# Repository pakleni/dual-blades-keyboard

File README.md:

# Dual Blades

## Images
### Keyboard Layout

### Plates

### PCB

## Features
* Split, wireless
* ZMK firmware
* nice!nano mcu
* nice!view display
* rotary encoders
* Column-staggered 44 key layout (inspired by the [Void Ergo S](https://github.com/victorlucachi/void_ergo))
* Switch-agnostic - hybrid MX/Alps PCB footprints + combo plate cutout
* Floating PCB plate
* LiPo batteries

## Firmware
[ZMK Keyboard Dual Blades](https://github.com/pakleni/zmk-keyboard-dual-blades)

## Bill of Materials

| Qty | Part |
|----:|------|
| 1 | [Matias Click Switch (box of 200)](https://matias.store/products/matias-click-switch-box-of-200) |
| 1 | [Keycap set - black blank Planck](https://matias.store/products/keycap-set-black-blank-planck) |
| 2 | [Encoder knobs](https://splitkb.com/products/knurled-metal-encoder-knob) |
| 2 | [nice!view](https://splitkb.com/products/nice-view) |
| 2 | [nice!nano](https://splitkb.com/products/nice-nano) |
| 1 | [Wireless Controller Expansion Bundle](https://splitkb.com/products/wireless-controller-expansion-bundle) |
| 1 | [THT 1N4148 diodes (100 pcs)](https://splitkb.com/products/tht-diodes) |
| 1 | [Linear rotary encoder](https://splitkb.com/products/linear-rotary-encoder) |
| 1 | [Tactile rotary encoder](https://splitkb.com/products/industrial-rotary-encoder) |
| 1 | [Reset buttons - **side push** (set of two)](https://splitkb.com/products/reset-buttons) |
| 2 | [Mill-Max Low Profile Sockets (with Headers)](https://splitkb.com/products/mill-max-low-profile-sockets) |
| 1 | [M2 screws - **4 mm**(set of 50)](https://splitkb.com/products/m2-screws) |
| 1 | [Brass M2 spacers - **8 mm** (set of 50)](https://splitkb.com/products/brass-m2-spacers) |
| 2 | [301230 LiPo (check polarity)](https://www.aliexpress.com/item/1005005348368664.html) |

## Used
* http://www.keyboard-layout-editor.com
* http://builder.swillkb.com
* https://librecad.org
* https://www.kicad.org

This work is licensed under a [Creative Commons Attribution-NonCommercial-ShareAlike 4.0 International License](https://creativecommons.org/licenses/by-nc-sa/4.0/).

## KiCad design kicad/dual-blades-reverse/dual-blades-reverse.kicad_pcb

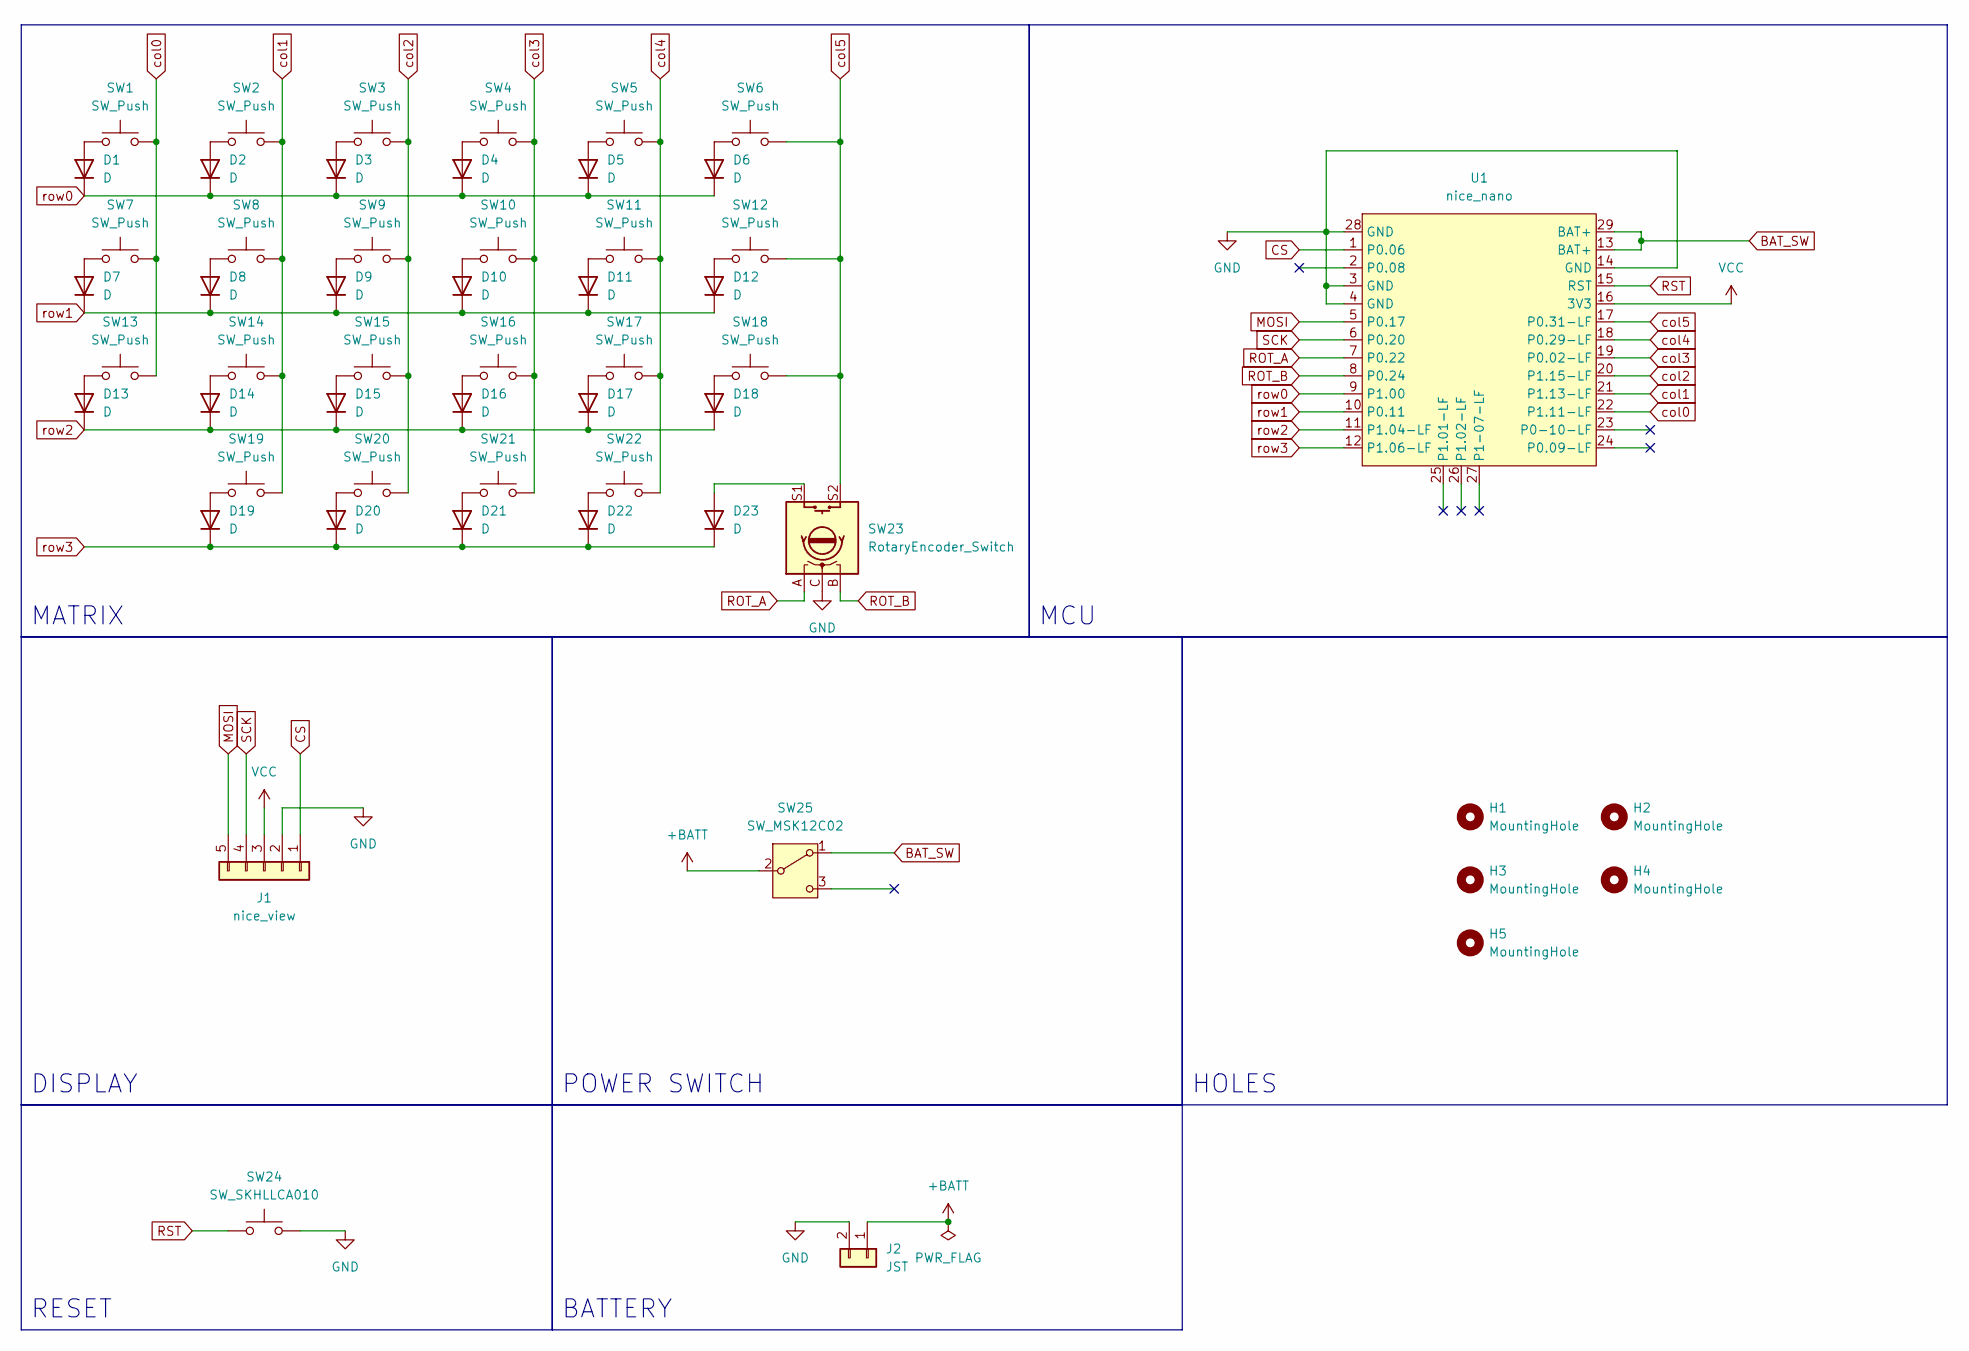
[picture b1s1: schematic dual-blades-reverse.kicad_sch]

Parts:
D1, D2, D3, D4, D5, D6, D7, D8, D9, D10, D11, D12, D13, D14, D15, D16, D17, D18, D19, D20, D21, D22, D23: D; D_DO-35_SOD27_P7.62mm_Horizontal
H1, H2, H3, H4, H5: MountingHole; MountingHole_4.3mm_M4
J1: nice_view; PinHeader_1x05_P2.54mm_Vertical
J2: JST; JST_PH_S2B-PH-K_1x02_P2.00mm_Horizontal
SW1, SW2, SW3, SW4, SW5, SW6, SW7, SW8, SW9, SW10, SW11, SW12, SW13, SW14, SW15, SW16, SW17, SW18, SW19, SW20, SW21, SW22: SW_Push; SW_Alps_MX_1u
SW23: RotaryEncoder_Switch; ROT_Alps_EC11E-Switch
SW24: SW_SKHLLCA010
SW25: SW_MSK12C02; SW_MSK12C02-HB
U1: nice_nano; nice_nano_AH_USBup

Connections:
+BATT: J2.1, SW25.2 (B)
BAT_SW: SW25.1 (A), U1.13 (BAT+), U1.29 (BAT+)
CS: J1.1, U1.1 (P0.06)
GND: J1.2, J2.2, SW23.C, SW24.2, U1.3 (GND), U1.4 (GND), U1.14 (GND), U1.28 (GND)
MOSI: J1.5, U1.5 (P0.17)
unnamed: D1.2 (A), SW1.1
unnamed: D2.2 (A), SW2.1
unnamed: D3.2 (A), SW3.1
unnamed: D4.2 (A), SW4.1
unnamed: D5.2 (A), SW5.1
unnamed: D6.2 (A), SW6.1
unnamed: D7.2 (A), SW7.1
unnamed: D8.2 (A), SW8.1
unnamed: D9.2 (A), SW9.1
unnamed: D10.2 (A), SW10.1
unnamed: D11.2 (A), SW11.1
unnamed: D12.2 (A), SW12.1
unnamed: D13.2 (A), SW13.1
unnamed: D14.2 (A), SW14.1
unnamed: D15.2 (A), SW15.1
unnamed: D16.2 (A), SW16.1
unnamed: D17.2 (A), SW17.1
unnamed: D18.2 (A), SW18.1
unnamed: D19.2 (A), SW19.1
unnamed: D20.2 (A), SW20.1
unnamed: D21.2 (A), SW21.1
unnamed: D22.2 (A), SW22.1
unnamed: D23.2 (A), SW23.S1
ROT_A: SW23.A, U1.7 (P0.22)
ROT_B: SW23.B, U1.8 (P0.24)
RST: SW24.1, U1.15 (RST)
SCK: J1.4, U1.6 (P0.20)
VCC: J1.3, U1.16 (3V3)
col0: SW1.2, SW7.2, SW13.2, U1.22 (P1.11-LF)
col1: SW2.2, SW8.2, SW14.2, SW19.2, U1.21 (P1.13-LF)
col2: SW3.2, SW9.2, SW15.2, SW20.2, U1.20 (P1.15-LF)
col3: SW4.2, SW10.2, SW16.2, SW21.2, U1.19 (P0.02-LF)
col4: SW5.2, SW11.2, SW17.2, SW22.2, U1.18 (P0.29-LF)
col5: SW6.2, SW12.2, SW18.2, SW23.S2, U1.17 (P0.31-LF)
row0: D1.1 (K), D2.1 (K), D3.1 (K), D4.1 (K), D5.1 (K), D6.1 (K), U1.9 (P1.00)
row1: D7.1 (K), D8.1 (K), D9.1 (K), D10.1 (K), D11.1 (K), D12.1 (K), U1.10 (P0.11)
row2: D13.1 (K), D14.1 (K), D15.1 (K), D16.1 (K), D17.1 (K), D18.1 (K), U1.11 (P1.04-LF)
row3: D19.1 (K), D20.1 (K), D21.1 (K), D22.1 (K), D23.1 (K), U1.12 (P1.06-LF)

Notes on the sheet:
HOLES
RESET
BATTERY
MATRIX
DISPLAY
POWER SWITCH
MCU

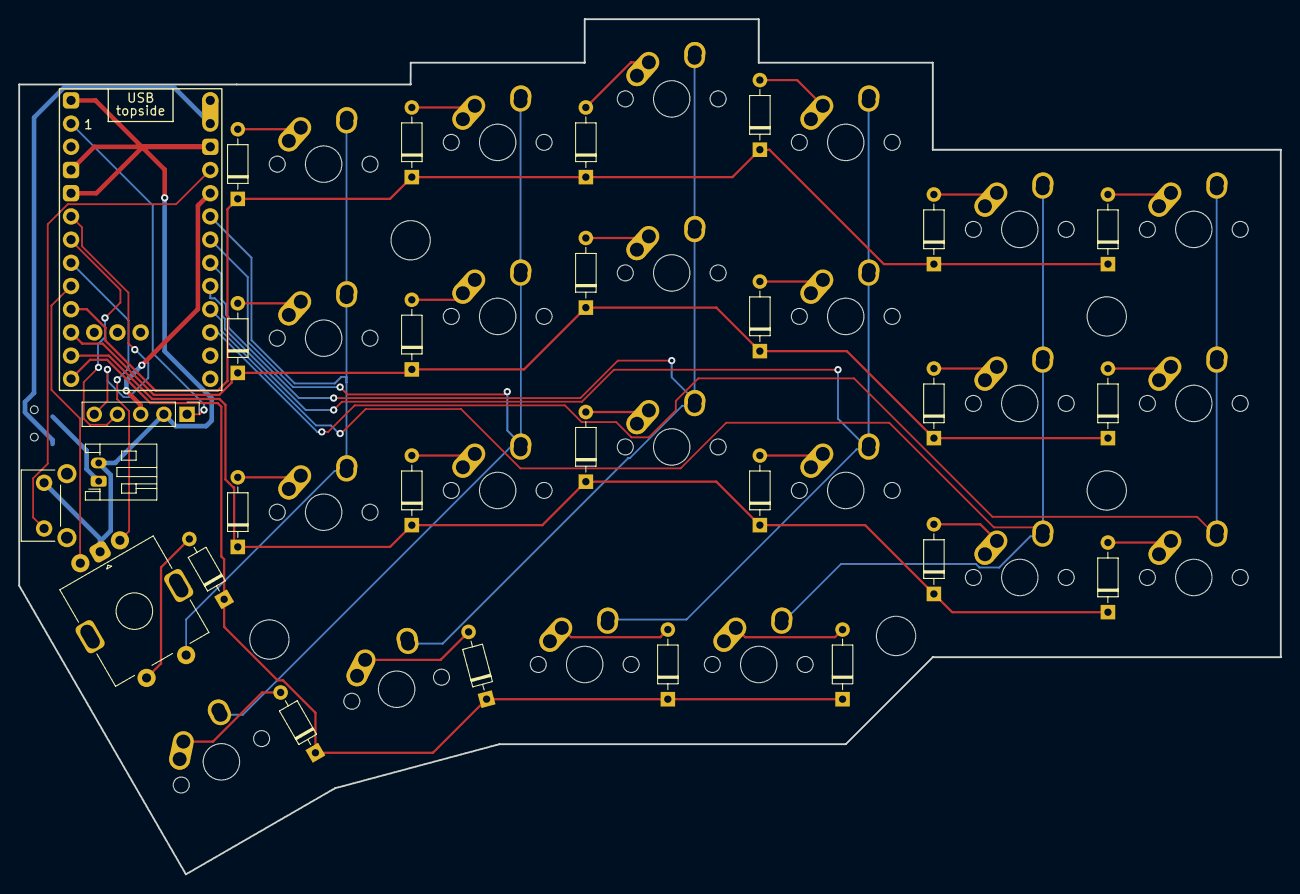
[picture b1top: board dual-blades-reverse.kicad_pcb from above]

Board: 2 copper layers, 138.1 x 93.6 mm, 56 parts (1 on the bottom side), 43 nets.

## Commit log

2026-06-23 update pcb gerbers and add keyboard image

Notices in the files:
README.md:
License: CC BY-NC-SA 4.0
